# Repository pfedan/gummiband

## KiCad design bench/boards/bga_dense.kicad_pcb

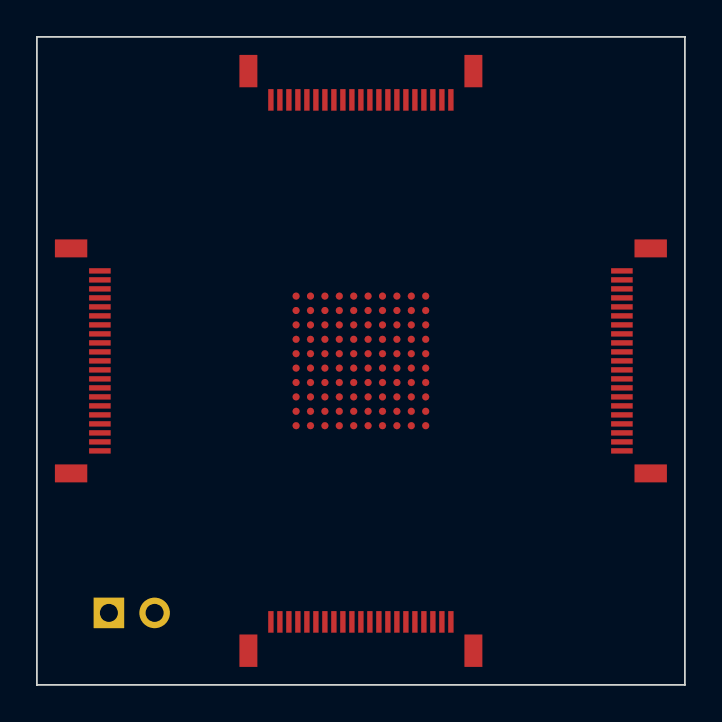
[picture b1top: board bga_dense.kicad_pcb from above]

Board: 4 copper layers, 36.0 x 36.0 mm, 6 parts (0 on the bottom side), 86 nets, no tracks yet.

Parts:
J1, J2, J3, J4: FPC; FPC-21P-0.5mm
J5: Conn; PinHeader_1x02
U1: FPGA; BGA-100

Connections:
+3V3: J5.2, U1.D5, U1.D7, U1.E4, U1.E6, U1.F5, U1.F7, U1.G4, U1.G6
B0_0: J1.1, U1.A1
B0_1: J1.2, U1.A2
B0_2: J1.3, U1.B2
B0_3: J1.4, U1.A3
B0_4: J1.5, U1.B3
B0_5: J1.6, U1.C3
B0_6: J1.7, U1.A4
B0_7: J1.8, U1.B4
B0_8: J1.9, U1.C4
B0_9: J1.10, U1.A5
B0_10: J1.11, U1.B5
B0_11: J1.12, U1.C5
B0_12: J1.13, U1.A6
B0_13: J1.14, U1.B6
B0_14: J1.15, U1.C6
B0_15: J1.16, U1.A7
B0_16: J1.17, U1.B7
B0_17: J1.18, U1.C7
B0_18: J1.19, U1.A8
B0_19: J1.20, U1.B8
B0_20: J1.21, U1.A9
B1_0: J2.1, U1.A10
B1_1: J2.2, U1.B10
B1_2: J2.3, U1.B9
B1_3: J2.4, U1.C10
B1_4: J2.5, U1.C9
B1_5: J2.6, U1.C8
B1_6: J2.7, U1.D10
B1_7: J2.8, U1.D9
B1_8: J2.9, U1.D8
B1_9: J2.10, U1.E10
B1_10: J2.11, U1.E9
B1_11: J2.12, U1.E8
B1_12: J2.13, U1.F10
B1_13: J2.14, U1.F9
B1_14: J2.15, U1.F8
B1_15: J2.16, U1.G10
B1_16: J2.17, U1.G9
B1_17: J2.18, U1.G8
B1_18: J2.19, U1.H10
B1_19: J2.20, U1.H9
B1_20: J2.21, U1.J10
B2_0: J3.21, U1.K2
B2_1: J3.20, U1.K3
B2_2: J3.19, U1.J3
B2_3: J3.18, U1.K4
B2_4: J3.17, U1.J4
B2_5: J3.16, U1.H4
B2_6: J3.15, U1.K5
B2_7: J3.14, U1.J5
B2_8: J3.13, U1.H5
B2_9: J3.12, U1.K6
B2_10: J3.11, U1.J6
B2_11: J3.10, U1.H6
B2_12: J3.9, U1.K7
B2_13: J3.8, U1.J7
B2_14: J3.7, U1.H7
B2_15: J3.6, U1.K8
B2_16: J3.5, U1.J8
B2_17: J3.4, U1.H8
B2_18: J3.3, U1.K9
B2_19: J3.2, U1.J9
B2_20: J3.1, U1.K10
B3_0: J4.21, U1.B1
B3_1: J4.20, U1.C1
B3_2: J4.19, U1.C2
B3_3: J4.18, U1.D1
B3_4: J4.17, U1.D2
B3_5: J4.16, U1.D3
B3_6: J4.15, U1.E1
B3_7: J4.14, U1.E2
B3_8: J4.13, U1.E3
B3_9: J4.12, U1.F1
B3_10: J4.11, U1.F2
B3_11: J4.10, U1.F3
B3_12: J4.9, U1.G1
B3_13: J4.8, U1.G2
B3_14: J4.7, U1.G3
B3_15: J4.6, U1.H1
B3_16: J4.5, U1.H2
B3_17: J4.4, U1.H3
B3_18: J4.3, U1.J1
B3_19: J4.2, U1.J2
B3_20: J4.1, U1.K1
GND: J5.1, U1.D4, U1.D6, U1.E5, U1.E7, U1.F4, U1.F6, U1.G5, U1.G7

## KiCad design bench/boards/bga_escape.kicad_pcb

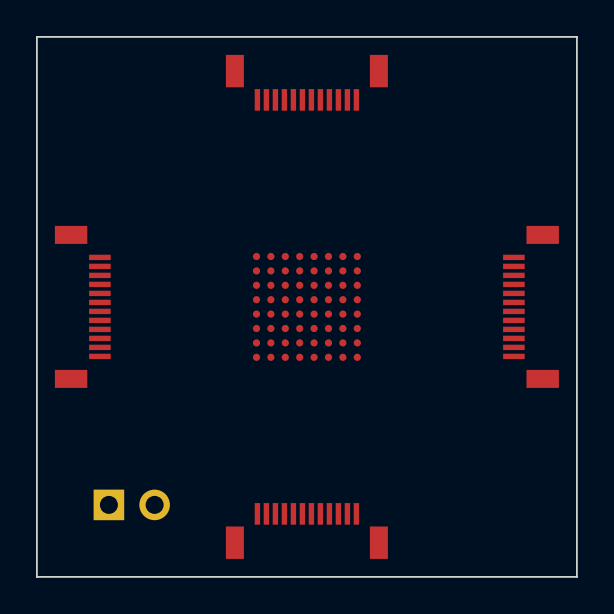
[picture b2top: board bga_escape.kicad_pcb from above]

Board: 4 copper layers, 30.0 x 30.0 mm, 6 parts (0 on the bottom side), 50 nets, no tracks yet.

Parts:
J1, J2, J3, J4: FPC; FPC-12P-0.5mm
J5: Conn; PinHeader_1x02
U1: FPGA; BGA-64

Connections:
+3V3: J5.2, U1.C4, U1.C6, U1.D3, U1.D5, U1.E4, U1.E6, U1.F3, U1.F5
B0_0: J1.1, U1.A1
B0_1: J1.2, U1.A2
B0_2: J1.3, U1.B2
B0_3: J1.4, U1.A3
B0_4: J1.5, U1.B3
B0_5: J1.6, U1.A4
B0_6: J1.7, U1.B4
B0_7: J1.8, U1.A5
B0_8: J1.9, U1.B5
B0_9: J1.10, U1.A6
B0_10: J1.11, U1.B6
B0_11: J1.12, U1.A7
B1_0: J2.1, U1.A8
B1_1: J2.2, U1.B8
B1_2: J2.3, U1.B7
B1_3: J2.4, U1.C8
B1_4: J2.5, U1.C7
B1_5: J2.6, U1.D8
B1_6: J2.7, U1.D7
B1_7: J2.8, U1.E8
B1_8: J2.9, U1.E7
B1_9: J2.10, U1.F8
B1_10: J2.11, U1.F7
B1_11: J2.12, U1.G8
B2_0: J3.12, U1.H2
B2_1: J3.11, U1.H3
B2_2: J3.10, U1.G3
B2_3: J3.9, U1.H4
B2_4: J3.8, U1.G4
B2_5: J3.7, U1.H5
B2_6: J3.6, U1.G5
B2_7: J3.5, U1.H6
B2_8: J3.4, U1.G6
B2_9: J3.3, U1.H7
B2_10: J3.2, U1.G7
B2_11: J3.1, U1.H8
B3_0: J4.12, U1.B1
B3_1: J4.11, U1.C1
B3_2: J4.10, U1.C2
B3_3: J4.9, U1.D1
B3_4: J4.8, U1.D2
B3_5: J4.7, U1.E1
B3_6: J4.6, U1.E2
B3_7: J4.5, U1.F1
B3_8: J4.4, U1.F2
B3_9: J4.3, U1.G1
B3_10: J4.2, U1.G2
B3_11: J4.1, U1.H1
GND: J5.1, U1.C3, U1.C5, U1.D4, U1.D6, U1.E3, U1.E5, U1.F4, U1.F6

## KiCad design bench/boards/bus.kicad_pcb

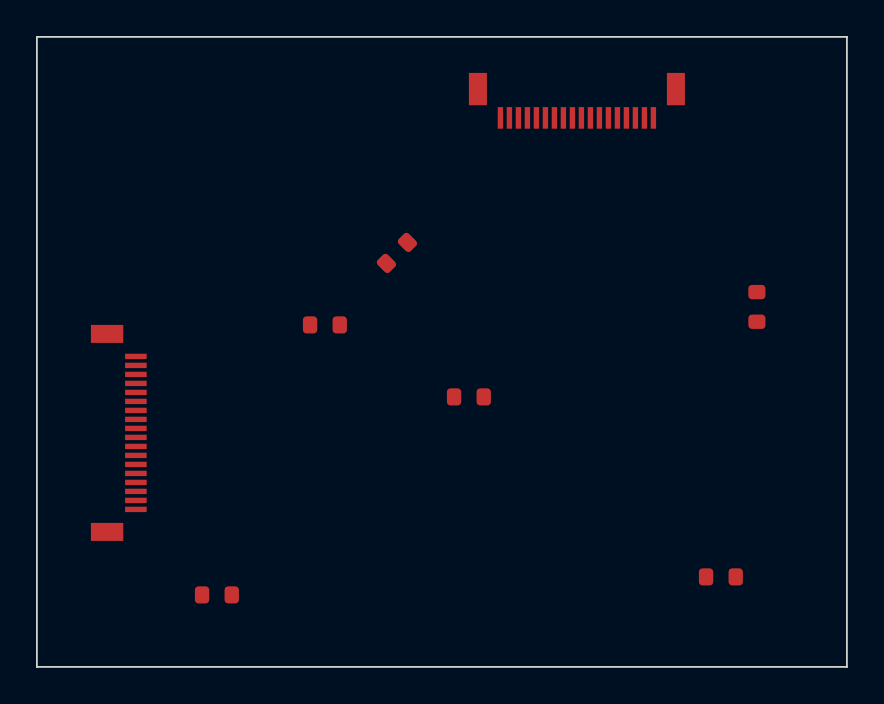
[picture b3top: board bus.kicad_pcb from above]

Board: 2 copper layers, 45.0 x 35.0 mm, 8 parts (0 on the bottom side), 20 nets, no tracks yet.

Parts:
J1, J2: FPC; FPC-18P-0.5mm
R1, R2, R3, R4, R5, R6: 10k; R_0603

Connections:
D0: J1.17, J2.2
D1: J1.16, J2.3
D2: J1.15, J2.4
D3: J1.14, J2.5
D4: J1.13, J2.6
D5: J1.12, J2.7
D6: J1.11, J2.8
D7: J1.10, J2.9
D8: J1.9, J2.10
D9: J1.8, J2.11
D10: J1.7, J2.12
D11: J1.6, J2.13
D12: J1.5, J2.14
D13: J1.4, J2.15
D14: J1.3, J2.16
D15: J1.2, J2.17
GND: J1.1, J1.18, J2.1, J2.18
P1: R1.1, R4.1
P2: R2.1, R5.1
P3: R3.1, R6.1

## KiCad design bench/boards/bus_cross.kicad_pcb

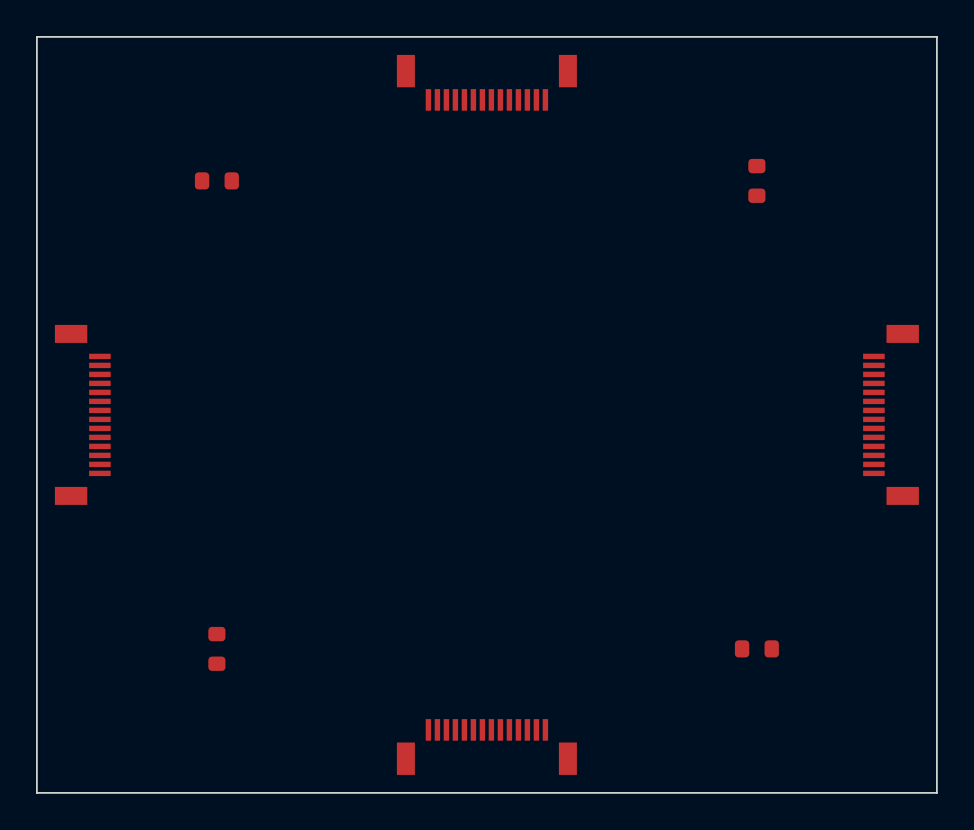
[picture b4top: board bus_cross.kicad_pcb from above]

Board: 2 copper layers, 50.0 x 42.0 mm, 8 parts (0 on the bottom side), 27 nets, no tracks yet.

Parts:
J1, J2, J3, J4: FPC; FPC-14P-0.5mm
R1, R2, R3, R4: 10k; R_0603

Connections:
A0: J1.13, J2.2
A1: J1.12, J2.3
A2: J1.11, J2.4
A3: J1.10, J2.5
A4: J1.9, J2.6
A5: J1.8, J2.7
A6: J1.7, J2.8
A7: J1.6, J2.9
A8: J1.5, J2.10
A9: J1.4, J2.11
A10: J1.3, J2.12
A11: J1.2, J2.13
B0: J3.2, J4.13
B1: J3.3, J4.12
B2: J3.4, J4.11
B3: J3.5, J4.10
B4: J3.6, J4.9
B5: J3.7, J4.8
B6: J3.8, J4.7
B7: J3.9, J4.6
B8: J3.10, J4.5
B9: J3.11, J4.4
B10: J3.12, J4.3
B11: J3.13, J4.2
GND: J1.1, J1.14, J2.1, J2.14, J3.1, J3.14, J4.1, J4.14, R1.2, R2.2, R3.2, R4.2
L0: R1.1, R2.1
L1: R3.1, R4.1

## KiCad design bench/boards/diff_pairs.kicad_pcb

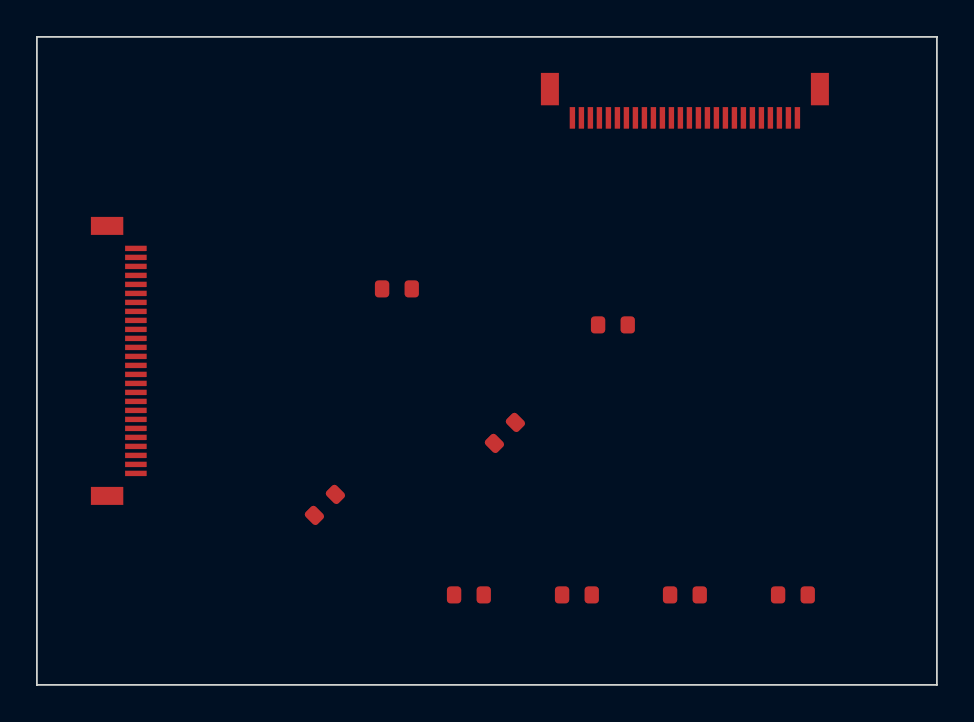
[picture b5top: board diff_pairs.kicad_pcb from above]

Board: 2 copper layers, 50.0 x 36.0 mm, 10 parts (0 on the bottom side), 29 nets, no tracks yet.

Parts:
J1, J2: FPC; FPC-26P-0.5mm
R1, R2, R3, R4, R5, R6, R7, R8: 10k; R_0603

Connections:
G0: J1.23, J2.4
G1: J1.20, J2.7
G2: J1.17, J2.10
G3: J1.14, J2.13
G4: J1.11, J2.16
G5: J1.8, J2.19
G6: J1.5, J2.22
G7: J1.2, J2.25
GND: J1.1, J1.26, J2.1, J2.26
L0_N: J1.24, J2.3
L0_P: J1.25, J2.2
L1_N: J1.21, J2.6
L1_P: J1.22, J2.5
L2_N: J1.18, J2.9
L2_P: J1.19, J2.8
L3_N: J1.15, J2.12
L3_P: J1.16, J2.11
L4_N: J1.12, J2.15
L4_P: J1.13, J2.14
L5_N: J1.9, J2.18
L5_P: J1.10, J2.17
L6_N: J1.6, J2.21
L6_P: J1.7, J2.20
L7_N: J1.3, J2.24
L7_P: J1.4, J2.23
P1: R1.1, R5.1
P2: R2.1, R6.1
P3: R3.1, R7.1
P4: R4.1, R8.1

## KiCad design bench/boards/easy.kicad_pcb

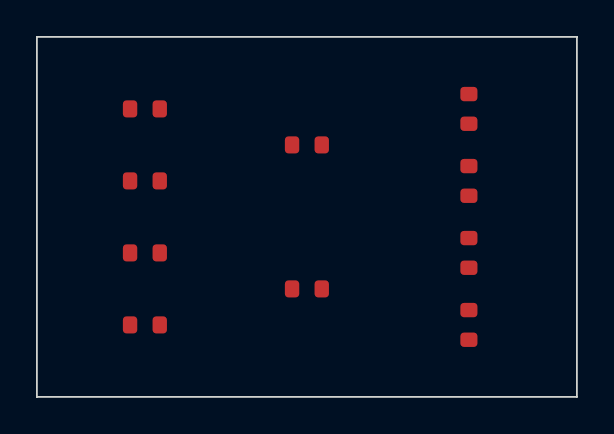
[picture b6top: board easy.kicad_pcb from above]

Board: 2 copper layers, 30.0 x 20.0 mm, 10 parts (0 on the bottom side), 9 nets, no tracks yet.

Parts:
C1, C2: 100n; C_0603
R1, R2, R3, R4, R5, R6, R7, R8: 10k; R_0603

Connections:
A: R1.1, R2.1
B: R3.1, R4.1
C: C1.2, R5.2
D: C2.2, R8.2
E: C1.1, C2.1
N1: R1.2, R5.1
N2: R2.2, R6.1
N3: R3.2, R7.1
N4: R4.2, R8.1

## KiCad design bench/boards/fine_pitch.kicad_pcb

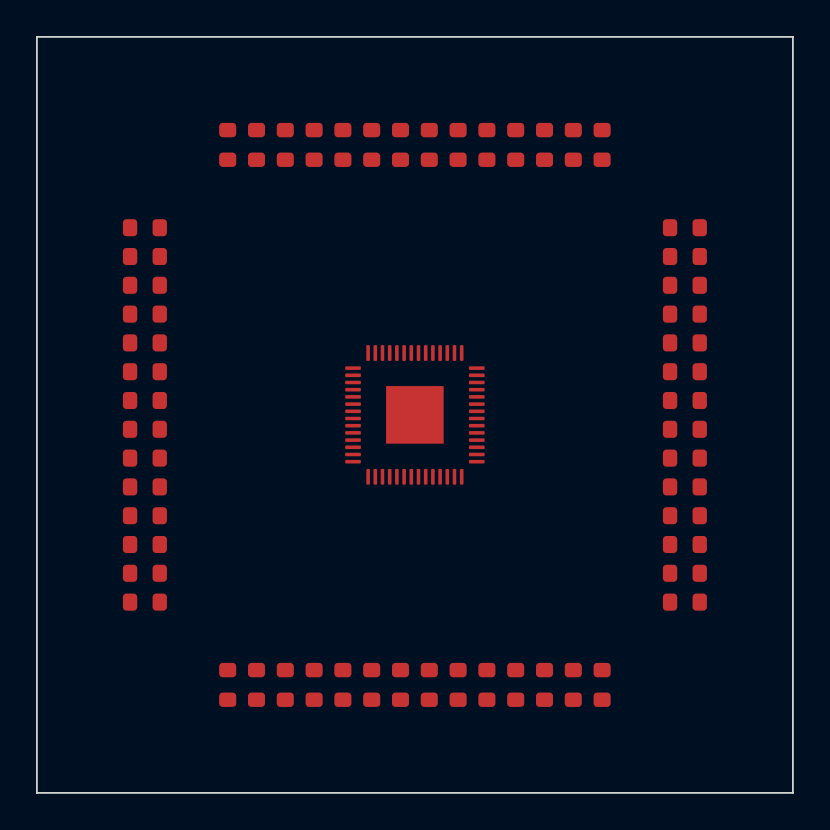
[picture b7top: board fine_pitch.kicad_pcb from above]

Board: 2 copper layers, 42.0 x 42.0 mm, 57 parts (0 on the bottom side), 57 nets, no tracks yet.

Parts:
R1, R2, R3, R4, R5, R6, R7, R8, R9, R10, R11, R12, R13, R14, R15, R16, R17, R18, R19, R20, R21, R22, R23, R24, R25, R26, R27, R28, R29, R30, R31, R32, R33, R34, R35, R36, R37, R38, R39, R40, R41, R42, R43, R44, R45, R46, R47, R48, R49, R50, R51, R52, R53, R54, R55, R56: 10k; R_0603
U1: MCU; QFN-56

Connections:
F1: R1.1, U1.1
F2: R2.1, U1.2
F3: R3.1, U1.3
F4: R4.1, U1.4
F5: R5.1, U1.5
F6: R6.1, U1.6
F7: R7.1, U1.7
F8: R8.1, U1.8
F9: R9.1, U1.9
F10: R10.1, U1.10
F11: R11.1, U1.11
F12: R12.1, U1.12
F13: R13.1, U1.13
F14: R14.1, U1.14
F15: R15.1, U1.15
F16: R16.1, U1.16
F17: R17.1, U1.17
F18: R18.1, U1.18
F19: R19.1, U1.19
F20: R20.1, U1.20
F21: R21.1, U1.21
F22: R22.1, U1.22
F23: R23.1, U1.23
F24: R24.1, U1.24
F25: R25.1, U1.25
F26: R26.1, U1.26
F27: R27.1, U1.27
F28: R28.1, U1.28
F29: R29.1, U1.42
F30: R30.1, U1.41
F31: R31.1, U1.40
F32: R32.1, U1.39
F33: R33.1, U1.38
F34: R34.1, U1.37
F35: R35.1, U1.36
F36: R36.1, U1.35
F37: R37.1, U1.34
F38: R38.1, U1.33
F39: R39.1, U1.32
F40: R40.1, U1.31
F41: R41.1, U1.30
F42: R42.1, U1.29
F43: R43.1, U1.56
F44: R44.1, U1.55
F45: R45.1, U1.54
F46: R46.1, U1.53
F47: R47.1, U1.52
F48: R48.1, U1.51
F49: R49.1, U1.50
F50: R50.1, U1.49
F51: R51.1, U1.48
F52: R52.1, U1.47
F53: R53.1, U1.46
F54: R54.1, U1.45
F55: R55.1, U1.44
F56: R56.1, U1.43
GND: R1.2, R2.2, R3.2, R4.2, R5.2, R6.2, R7.2, R8.2, R9.2, R10.2, R11.2, R12.2, R13.2, R14.2, R15.2, R16.2, R17.2, R18.2, R19.2, R20.2, R21.2, R22.2, R23.2, R24.2, R25.2, R26.2, R27.2, R28.2, R29.2, R30.2, R31.2, R32.2, R33.2, R34.2, R35.2, R36.2, R37.2, R38.2, R39.2, R40.2, R41.2, R42.2, R43.2, R44.2, R45.2, R46.2, R47.2, R48.2, R49.2, R50.2, R51.2, R52.2, R53.2, R54.2, R55.2, R56.2, U1.57
